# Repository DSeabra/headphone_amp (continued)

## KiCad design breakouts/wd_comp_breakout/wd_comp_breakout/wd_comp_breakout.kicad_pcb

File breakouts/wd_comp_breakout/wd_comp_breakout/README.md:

# Watchdog comparator breakout (TLV7011), Rev A rework board

**Date:** 2026-11-21 (v4: four M2.5 unplated mounting holes, rounded corners; JST SH 6-pin right-angle connector, full value silkscreen, RV1 removed) · Implements the comparator from `RevA-Watchdog-Comparator-Plan.md` / `RevA-Comparator-Starting-Values.md` (Set A) as a small board you wire into a Rev A unit in place of the U7A → AUDIO_DETECT path. Not built or measured; thresholds are calculated.

## Board

- 25.4 × 25.4 mm (1 × 1 in), 2 layers, 1.6 mm, **2 mm corner radius**.
- **Four M2.5 mounting holes**: 2.7 mm unplated (NPTH), centred 3.0 mm from each edge, so the hole edge sits 1.65 mm from the board edge. Hole centres are 19.4 mm apart in both directions. Each hole has a 3 mm radius keepout (6 mm diameter, enough for a 5 mm screw head, M2.5 washer or standoff): no copper, vias or silk inside it, and the bottom GND pour is cut back to 3.2 mm. Unplated holes add no copper rings on the bottom, so VHB mounting still works; use screws or VHB, or both.
- **Everything is surface-mount on the top side**: 0603 passives, SOT-23-5 comparator, and J1 = JST SH 6-pin right-angle header (SM06B-SRSS-TB, 1.0 mm pitch). The bottom has no through-hole pads, only tented vias, bottom traces and the GND pour under solder mask. That makes it flat for VHB.
- **J1 placement:** centred on the bottom edge with the opening facing out, so the plug goes in from the board edge. The mounting tabs are toward the edge, 0.5 mm in from it, and the header body ends about 0.8 mm inside the edge. Footprint geometry matches KiCad's stock `Connector_JST:JST_SH_SM06B-SRSS-TB_1x06-1MP_P1.00mm_Horizontal` (signal pads 0.6 × 1.55 mm at y = −2, tabs 1.2 × 1.8 mm at ±3.8, +1.875). The tabs are left unconnected (mechanical only).
- **Mounting:** VHB on the bottom (the silk there says so), or M2.5 screws/standoffs through the corner holes. The bottom silk (Set A values and the hookup map) will be hidden once mounted, so the same information is in this README.
- **Top silk:** reference, value and "DNP" next to every part (0.8 mm text, 0.13 mm stroke, above OSH Park's 5 mil minimum line width), a J1 pin legend on the left edge (J1-1 GND … J1-6 GND, moved out of the hole keepouts) plus a pin‑1 triangle at the connector, and "SET A" by the reference divider.
- Rules used: 0.25 mm signal / 0.4 mm power tracks, ≥ 0.35 mm copper clearance, 0.6/0.3 mm vias, ≥ 1.9 mm copper to edge. OSH Park 2-layer limits are 6 mil / 6 mil, 10 mil drill; Board Setup is preset to those.
- Bottom layer has a GND pour (zone, **unfilled in the file**). Every GND pad is also connected by a track, so the board works even if the pour is never filled.

## J1 pinout (JST SH 6; pin 1 is on the left looking down at the top with the opening toward you)

| Pin | Silk | Net | Wire to on Rev A |
|---|---|---|---|
| 1 | GND | GND | U8 pin 7 |
| 2 | DET | AUDIO_DETECT (comparator OUT) | U8 pin 9 / TP8 side **after cutting** AUDIO_DETECT between U7.2 and U8.9 (the diagonal F.Cu segment near (95.64, 77.26)) |
| 3 | THR | ENV_THRESHOLD (comparator IN+) | R30/R31 junction (also U7 pin 1) |
| 4 | VL | V_LOGIC (2.5 V) | C26 |
| 5 | REF | VREF (IN−) | probe only, expect about 0.30 V (calc) |
| 6 | GND | GND | probe ground / second GND wire |

The SH cable's far end gets soldered to the Rev A points above. Pin numbering follows the housing, so check which wire color lands on pin 1 in your cable before soldering the Rev A end.

THR is a high-impedance node (about 235 kΩ from R30 ∥ R31, with R3 feeding back). Keep that wire short and twisted with a GND wire. If it picks up hum, fit C3 (about 1 nF; 0.24 ms against R30 ∥ R31, negligible next to the 0.2 s envelope).

## Schematic summary

- U1 TLV7011 on V_LOGIC with C1 100 nF. Pinout per TI SLVSDM5F (SOT-23-5): 1 OUT, 2 VEE, 3 IN+, 4 IN−, 5 VCC.
- IN− = Vref from R1 (Rt) / R2 (Rb) with C2 10 nF.
- R3 (Rh) from OUT to IN+ for hysteresis.
- Rb = R2 + R5, two 0603s in series to GND (R5 = 0 Ω for Set A). Swap either one to tune. For an adjustable threshold, remove R5 and wire a small trimmer across its pads. The through-hole RV1 footprint from v1 is gone, because its leads would have stuck out of the bottom.
- R4 (DNP) pull-up to V_LOGIC, only needed for the open-drain TLV7021.

Math (also printed on the schematic and bottom silk), R30 = R31 = 470 k on the main board:

- Vref = 2.5 × 30 k / 250 k = 0.30 V
- Trip (at ENV_HOLD) = Vref × (1 + R30/R31 + R30/R3) = 0.30 × 2.1 = 0.63 V
- Release = Trip − V_LOGIC × R30/R3 = 0.63 − 0.25 = 0.38 V
- The TLV7011's internal hysteresis moves each threshold by about 4 mV (simulation note).

## BOM

| Ref | Value | Package | Fit | Note |
|---|---|---|---|---|
| U1 | TLV7011DBVR (silk/value "TLV7011") | SOT-23-5 | yes | TLV7021DBVR also fits (then fit R4) |
| R1 | 220 k 1 % | 0603 | yes | Rt |
| R2 | 30 k 1 % | 0603 | yes | Rb; Set B and B+: 20 k |
| R3 | 4.7 M 1 % | 0603 | yes | Rh; Set B and B+: 10 M |
| R4 | 100 k | 0603 | DNP | TLV7021 only |
| R5 | 0 Ω | 0603 | yes | second Rb element (Rb = R2 + R5); or a solder bridge |
| C1 | 100 nF X7R | 0603 | yes | |
| C2 | 10 nF X7R | 0603 | yes | |
| C3 | 1 nF C0G | 0603 | DNP | IN+ filter, only if needed |
| H1–H4 | M2.5 mounting hole | 2.7 mm NPTH | — | no part; KiCad `MountingHole:MountingHole_2.7mm_M2.5` |
| J1 | JST SM06B-SRSS-TB(LF)(SN) | SH 6-pin R/A SMD | yes | mates with SHR-06V-S(-B) housing / pre-crimped SH cables (28 to 32 AWG) |

| Set | R2 | R3 | R5 | Trip / release at ENV_HOLD (calc) |
|---|---|---|---|---|
| A (default) | 30 k | 4.7 M | R5 0 Ω | 0.63 / 0.38 V |
| B | 20 k | 10 M | R5 0 Ω | 0.43 / 0.31 V |
| B+ | 20 k | 10 M | R5 removed, 20 k trimmer wired across R5 pads | 0.43 to 0.79 / 0.31 to 0.67 V |

## Before ordering (KiCad)

These files were generated by script without a KiCad install. I parsed them back and checked: every net fully routed, no shorts, clearances, track ends, copper-to-edge, silk on pads, and schematic netlist against PCB pad nets (27 pins, 0 mismatches), and silk size, silk-on-pad/via, silk-on-silk, no through-hole pads, a closed outline with 2 mm arcs, and the 3 mm hole keepouts (nearest copper 4.0 mm, nearest silk 3.1 mm from a hole centre). KiCad's own ERC and DRC have **not** been run.

1. Open `wd_comp_breakout.kicad_pro` in KiCad. The files are in KiCad 7 format, so KiCad 8 and later will convert them on save.
2. Schematic: run ERC. Expect at most library-mismatch warnings. The project library `wd_comp_breakout` holds TLV7011DBV and V_LOGIC (plus an unused R_Trim symbol), J1 uses the stock KiCad footprint name, so no project footprint library is needed.
3. PCB: press **B** (fill zones), then run DRC. A rotation-convention error on my side would show up here at once as unconnected pads. Optional: Tools → Update Footprints from Library to swap my hand-written copies of the stock SOT-23-5 / 0603 / JST SH / mounting-hole footprints for the library ones. Updating also resets the silk text positions, so only do it if you're happy to re-place the labels.
4. Save, then order:
   - OSH Park accepts `.kicad_pcb` directly but **does not refill zones**, so fill and save first. Their docs say they process with KiCad 8, so a file saved by a newer KiCad may not import.
   - Safer route from a newer KiCad: File → Plot Gerbers (F.Cu, B.Cu, F/B Mask, F/B Silk, Edge.Cuts) plus an Excellon drill file. Zip them and upload. Leave vias tented (the KiCad default) so the VHB side is all mask.

## After wiring (from the Starting Values note)

- Idle: THR about 0 V, DET low, REF about 0.30 V.
- Pluck, then hard strum: DET goes high, and releases about 0.2 s after the last note.
- Full drive and volume with nothing played: DET must stay low. This decides Set A versus B.
- Then D4, and the timed shutdown (about 10.2 min calc, or about 6 s with C23 temporarily at 6.8 nF).

## Files

- `wd_comp_breakout.kicad_pro / .kicad_sch / .kicad_pcb`: project, schematic, layout
- `wd_comp_breakout.kicad_sym`, `sym-lib-table`: project symbol library
- `preview_top.png`, `preview_bottom.png`, `preview_sch.png`: renders from my own plotter (approximate fonts), not KiCad

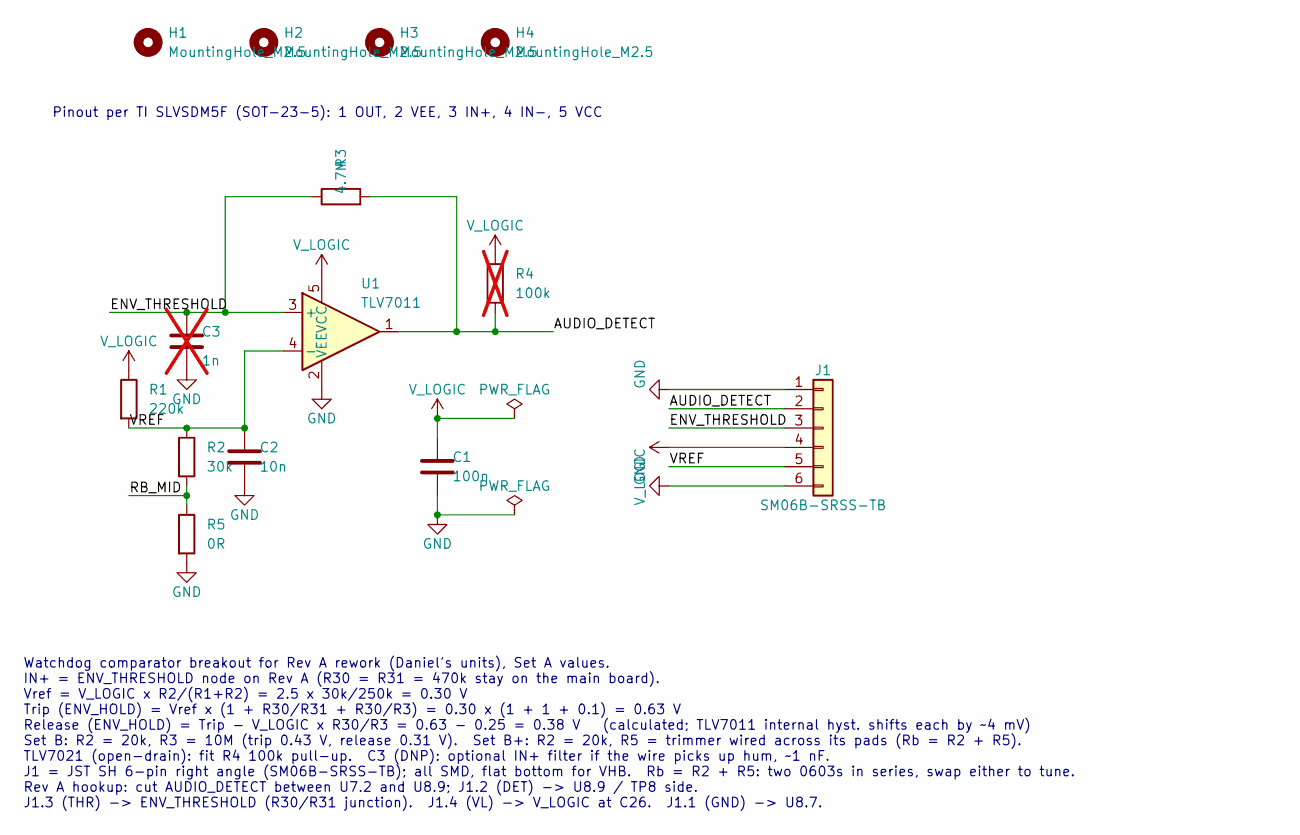
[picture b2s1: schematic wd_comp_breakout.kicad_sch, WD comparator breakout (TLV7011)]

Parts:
C1: 100n; C_0603_1608Metric
C2: 10n; C_0603_1608Metric
C3: 1n; C_0603_1608Metric; not fitted
H1, H2, H3, H4: MountingHole_M2.5; MountingHole_2.7mm_M2.5
J1: SM06B-SRSS-TB; JST_SH_SM06B-SRSS-TB_1x06-1MP_P1.00mm_Horizontal
R1: 220k; R_0603_1608Metric
R2: 30k; R_0603_1608Metric
R3: 4.7M; R_0603_1608Metric
R4: 100k; R_0603_1608Metric; not fitted
R5: 0R; R_0603_1608Metric
U1: TLV7011; SOT-23-5

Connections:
/AUDIO_DETECT: J1.2, R3.2, R4.2, U1.1
/ENV_THRESHOLD: C3.1, J1.3, R3.1, U1.3 (+)
/RB_MID: R2.2, R5.1
/VREF: C2.1, J1.5, R1.2, R2.1, U1.4 (-)
GND: C1.2, C2.2, C3.2, J1.1, J1.6, R5.2, U1.2 (VEE)
V_LOGIC: C1.1, J1.4, R1.1, R4.1, U1.5 (VCC)

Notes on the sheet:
Watchdog comparator breakout for Rev A rework (Daniel's units), Set A values. IN+ = ENV_THRESHOLD node on Rev A (R30 = R31 = 470k stay on the main board). Vref = V_LOGIC x R2/(R1+R2) = 2.5 x 30k/250k = 0.30 V Trip (ENV_HOLD) = Vref x (1 + R30/R31 + R30/R3) = 0.30 x (1 + 1 + 0.1) = 0.63 V Release (E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
Pinout per TI SLVSDM5F (SOT-23-5): 1 OUT, 2 VEE, 3 IN+, 4 IN-, 5 VCC

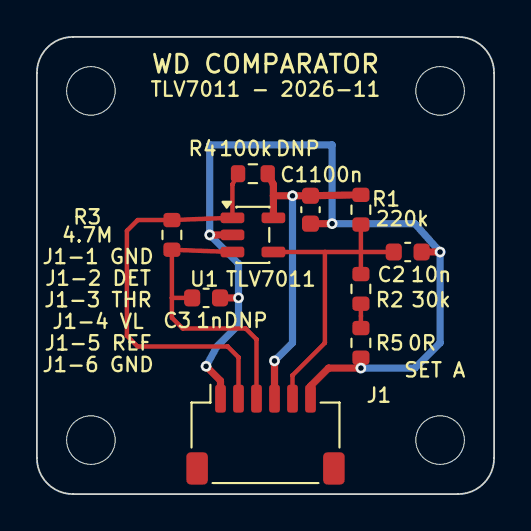
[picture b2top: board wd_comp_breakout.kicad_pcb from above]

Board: 2 copper layers, 25.4 x 25.4 mm, 14 parts (0 on the bottom side), 6 nets.

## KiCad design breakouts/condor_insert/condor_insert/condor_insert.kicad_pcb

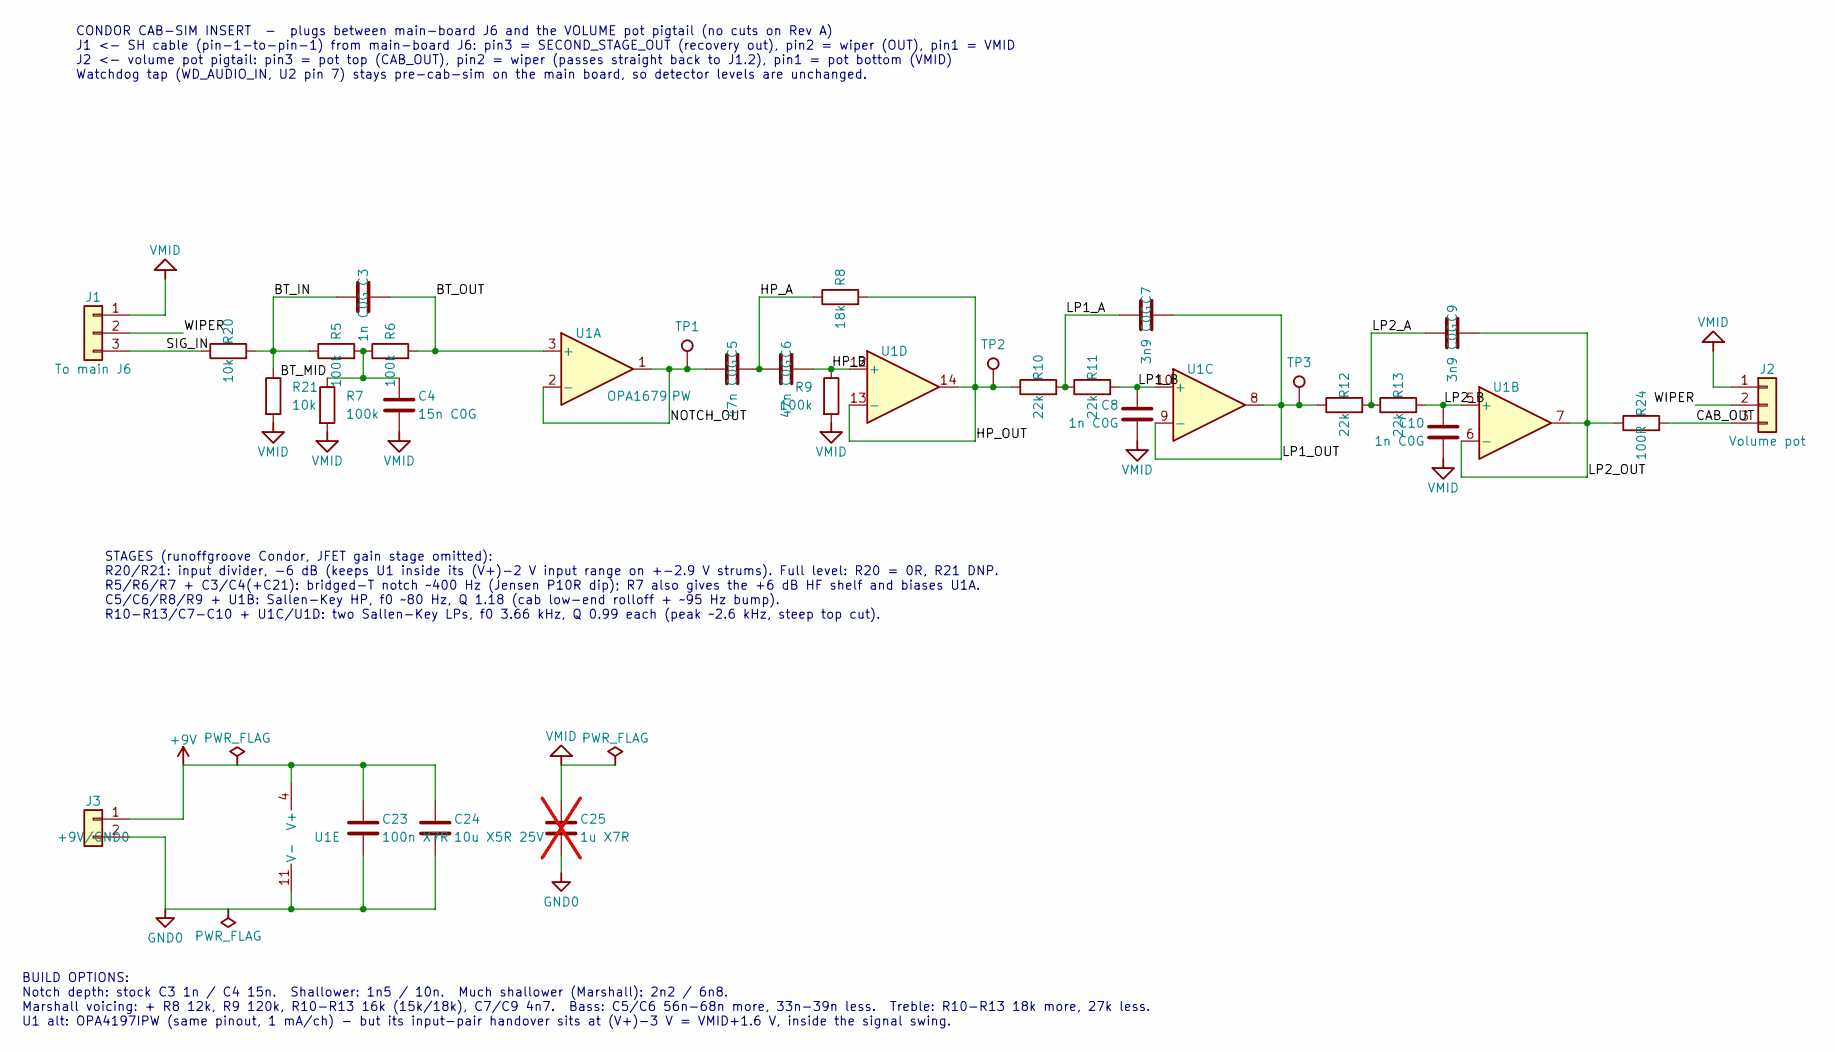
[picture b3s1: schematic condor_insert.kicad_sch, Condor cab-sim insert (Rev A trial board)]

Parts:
C3, C8, C10: 1n C0G; C_0603_1608Metric
C4: 15n C0G; C_0603_1608Metric
C5, C6: 47n C0G; C_0805_2012Metric
C7, C9: 3n9 C0G; C_0603_1608Metric
C23: 100n X7R; C_0603_1608Metric
C24: 10u X5R 25V; C_0805_2012Metric
C25: 1u X7R; C_0603_1608Metric; not fitted
J1: To main J6; JST_SH_SM03B-SRSS-TB_1x03-1MP_P1.00mm_Horizontal
J2: Volume pot; JST_SH_SM03B-SRSS-TB_1x03-1MP_P1.00mm_Horizontal
J3: +9V/GND0; PinHeader_1x02_P2.54mm_Vertical
R5, R6, R7, R9: 100k; R_0603_1608Metric
R8: 18k; R_0603_1608Metric
R10, R11, R12, R13: 22k; R_0603_1608Metric
R20, R21: 10k; R_0603_1608Metric
R24: 100R; R_0603_1608Metric
TP1: NOTCH; TestPoint_Pad_D1.0mm
TP2: HP; TestPoint_Pad_D1.0mm
TP3: LP1; TestPoint_Pad_D1.0mm
U1: OPA1679IPW; TSSOP-14_4.4x5mm_P0.65mm

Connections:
+9V: C23.1, C24.1, J3.1, U1.4 (V+)
/BT_IN: C3.1, R5.1, R20.2, R21.1
/BT_MID: C4.1, R5.2, R6.1, R7.1
/BT_OUT: C3.2, R6.2, U1.3 (+)
/CAB_OUT: J2.3, R24.2
/HP_A: C5.2, C6.1, R8.1
/HP_B: C6.2, R9.1, U1.12 (+)
/HP_OUT: R8.2, R10.1, TP2.1 (1_1), U1.13 (-), U1.14
/LP1_A: C7.1, R10.2, R11.1
/LP1_B: C8.1, R11.2, U1.10 (+)
/LP1_OUT: C7.2, R12.1, TP3.1 (1_1), U1.8, U1.9 (-)
/LP2_A: C9.1, R12.2, R13.1
/LP2_B: C10.1, R13.2, U1.5 (+)
/LP2_OUT: C9.2, R24.1, U1.6 (-), U1.7
/NOTCH_OUT: C5.1, TP1.1 (1_1), U1.1, U1.2 (-)
/SIG_IN: J1.3, R20.1
/WIPER: J1.2, J2.2
GND0: C23.2, C24.2, C25.2, J3.2, U1.11 (V-)
VMID: C4.2, C8.2, C10.2, C25.1, J1.1, J2.1, R7.2, R9.2, R21.2

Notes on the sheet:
CONDOR CAB-SIM INSERT - plugs between main-board J6 and the VOLUME pot pigtail (no cuts on Rev A) J1 <- SH cable (pin-1-to-pin-1) from main-board J6: pin3 = SECOND_STAGE_OUT (recovery out), pin2 = wiper (OUT), pin1 = VMID J2 <- volume pot pigtail: pin3 = pot top (CAB_OUT), pin2 = wiper (passes stra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
STAGES (runoffgroove Condor, JFET gain stage omitted): R20/R21: input divider, -6 dB (keeps U1 inside its (V+)-2 V input range on +-2.9 V strums). Full level: R20 = 0R, R21 DNP. R5/R6/R7 + C3/C4(+C21): bridged-T notch ~400 Hz (Jensen P10R dip); R7 also gives the +6 dB HF shelf and biases U1A. C5/C6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
BUILD OPTIONS: Notch depth: stock C3 1n / C4 15n. Shallower: 1n5 / 10n. Much shallower (Marshall): 2n2 / 6n8. Marshall voicing: + R8 12k, R9 120k, R10-R13 16k (15k/18k), C7/C9 4n7. Bass: C5/C6 56n-68n more, 33n-39n less. Treble: R10-R13 18k more, 27k less. U1 alt: OPA4197IPW (same pinout, 1 mA/ch) 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

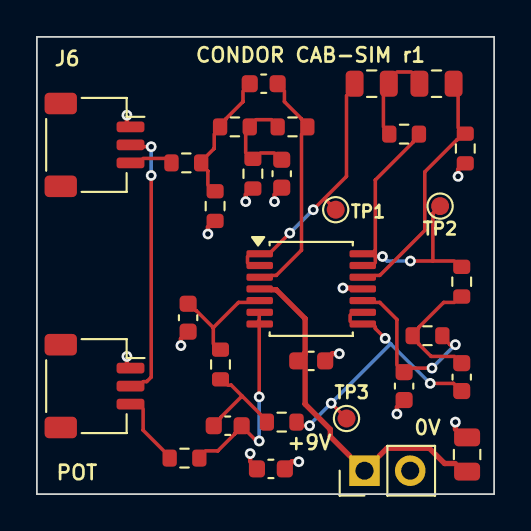
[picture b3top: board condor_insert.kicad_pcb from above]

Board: 4 copper layers, 25.4 x 25.4 mm, 30 parts (0 on the bottom side), 19 nets.
